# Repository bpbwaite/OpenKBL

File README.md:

# Open Keyboard Lights

OpenKeyBoardLights (okbl) is an embedded project for MIDI piano keyboards. \
The device sits above the keys of an 88-key piano, and illuminates when keys are played. \
To get the cost down, the light strip is mounted across 8 smaller PCBs that are soldered together. It's less expensive than some commercial options, and has more features!

*Technologies:* ESP32-C3, PlatformIO, KiCAD 10 - [Custom PCB](piano-pcb/), and a [3D printable case](models/)

## Usage

Revision 0:
- Turn the encoder to set the brightness.
- Press the encoder to open the settings menu
    - Press a lit key to change and preview its corresponding option.

## Roadmap

| Hardware Feature | Implemented |
|-|-|
| Accurate LED spacing | ✅ |
| Low resistance traces | ✅ |
| Newly improved PCB | 🚧 |
---
| Software Feature | Implemented |
|-|-|
| Various color modes | ✅ more coming soon |
| Demo mode (5 min timer) | ✅ |
| Control over serial | ✅ |
| Control with desktop app | 🚧 |
| Control over WiFi | 🚧 |
| Training mode | 🚧 |
| Hand mode (blue-green) neural model | 🚧 |
---

## Flash Binary

With PlatformIO (recommended):
```
cd keyboard-lights-firmware/
pio run -e release_seeed_xiao_esp32c3 -t upload
```
With esptool v4+, using a prebuilt image:
```
esptool.py --chip esp32c3 --port COMx --baud 460800 write_flash --flash_mode dio --flash_freq 80m --flash_size 4MB 0x0 okbl-firmware-<version>-merged.bin

```

## Building

- Open [keyboard-lights-firmware/](keyboard-lights-firmware/) with PlatformIO
- Set `-DPCB_REVISION` in `platformio.ini` to match your board.
- For testing without a piano, build with `-DKBL_USB_MIDI_DEBUG`. Type `help` to list commands.

## Assembly

- still todo: BOM, gerbers

## Credits

This project is MIT licensed, see [LICENSE](LICENSE). The firmware images include code from these
projects, each under its own license:

- [FastLED](https://github.com/FastLED/FastLED): MIT
- [Arduino MIDI Library](https://github.com/FortySevenEffects/arduino_midi_library): MIT
- [Arduino core for ESP32](https://github.com/espressif/arduino-esp32): LGPL-2.1
- [ESP-IDF](https://github.com/espressif/esp-idf): Apache-2.0

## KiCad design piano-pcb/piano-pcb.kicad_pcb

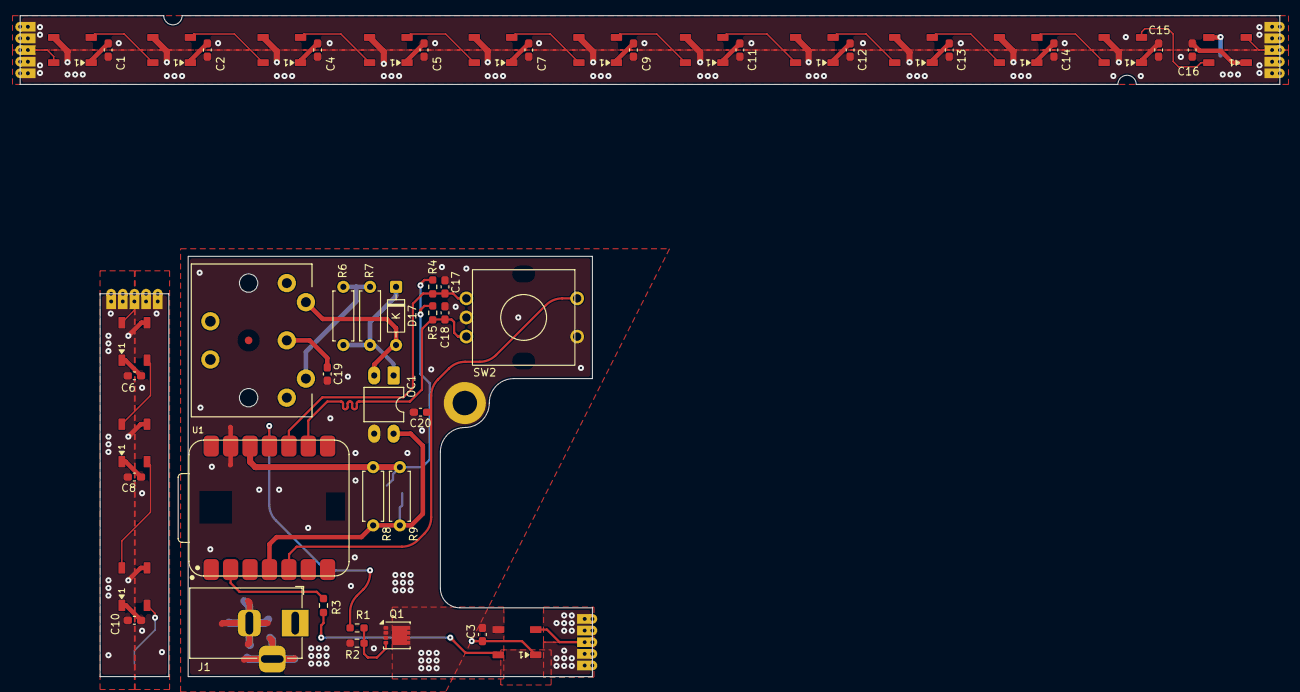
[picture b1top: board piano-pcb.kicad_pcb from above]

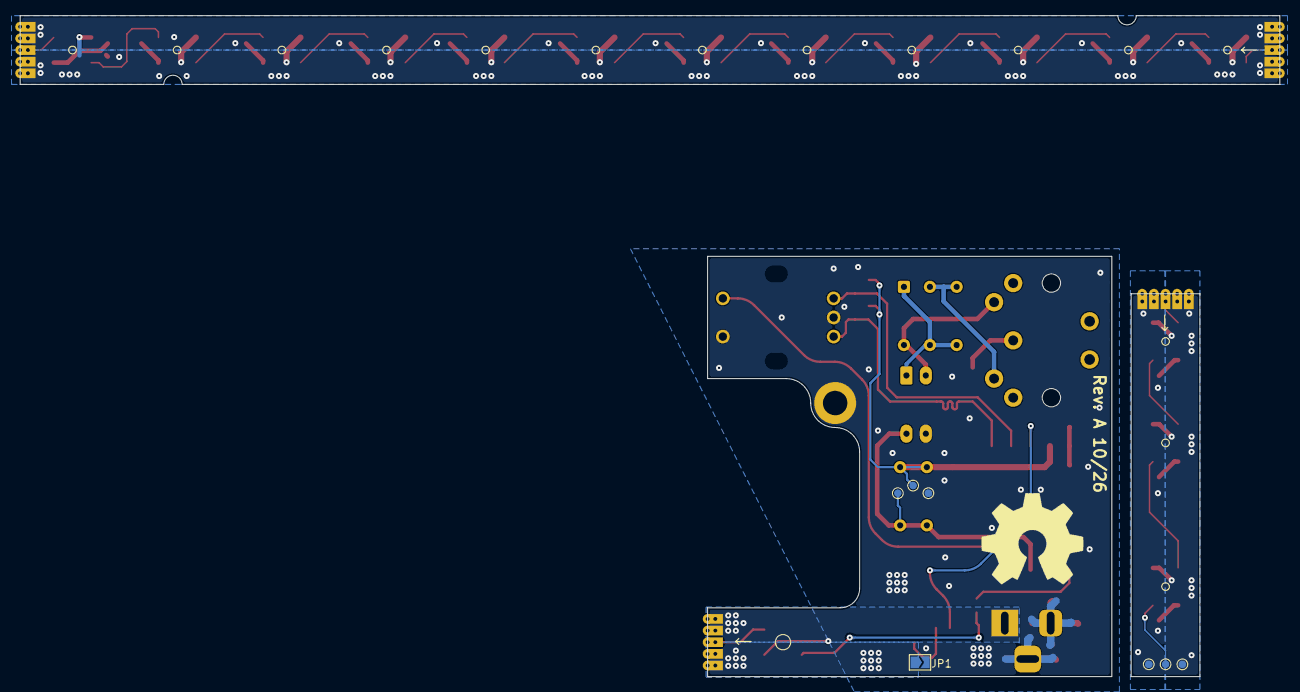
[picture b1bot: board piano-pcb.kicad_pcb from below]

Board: 2 copper layers, 164.9 x 86.5 mm, 66 parts (10 on the bottom side), 35 nets.

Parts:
C1, C2, C3, C4, C5, C6, C7, C8, C9, C10, C11, C12, C13, C14, C15, C16, C19: 100n; C_0603_1608Metric_Pad1.08x0.95mm_HandSolder
C17, C18, C20: 10n; C_0603_1608Metric_Pad1.08x0.95mm_HandSolder
D1, D2, D3, D4, D5, D6, D7, D8, D9, D10, D11, D12, D13, D14, D15, D16: WS2812B; LED_WS2812B_PLCC4_5.0x5.0mm_P3.2mm
D17: 1N914; D_DO-35_SOD27_P7.62mm_Horizontal
FID1: Fiducial; Fiducial_1mm_Mask3mm
H1: MountingHole_Pad; MountingHole_3.2mm_M3_ISO14580_Pad
J1: Barrel_Jack_MountingPin; BarrelJack_Horizontal
J2, J3, J4, J6: Conn_01x05; 1x5_SolderableEdgeConnector
J5: DIN-5_180degree; SameSky_SDS-50J_DIN-5-180_MIDI
JP1: SolderJumper_2_Open; SolderJumper-2_P1.3mm_Open_TrianglePad1.0x1.5mm
OC1: PC817; DIP-4_W7.62mm_LongPads
Q1: CSD17581Q3A; VSON-8_3.3x3.3mm_P0.65mm_NexFET
R1: 330; R_0603_1608Metric_Pad0.98x0.95mm_HandSolder
R2: 100k; R_0603_1608Metric_Pad0.98x0.95mm_HandSolder
R3: TBD; R_0603_1608Metric_Pad0.98x0.95mm_HandSolder
R4, R5: 10k; R_0603_1608Metric_Pad0.98x0.95mm_HandSolder
R6: 1k; R_Axial_DIN0207_L6.3mm_D2.5mm_P7.62mm_Horizontal
R7, R8: TBD; R_Axial_DIN0207_L6.3mm_D2.5mm_P7.62mm_Horizontal
R9: 680; R_Axial_DIN0207_L6.3mm_D2.5mm_P7.62mm_Horizontal
SW2: RotaryEncoder_Switch; Bourns_PEC11R-4x-Sx_RotaryEncoder
Sw1: Mechanical_Shape; OSHW-Symbol_13.4x12mm_SilkScreen
TP1, TP2, TP3, TP4, TP5, TP6: TestPoint; TestPoint_Pad_D1.0mm
U1: XIAO-RP2040-SMD

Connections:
+5V: C1.1, C2.1, C3.1, C4.1, C5.1, C6.1, C7.1, C8.1, C9.1, C10.1, C11.1, C12.1, C13.1, C14.1, C15.1, C16.1, D1.1 (VDD), D2.1 (VDD), D3.1 (VDD), D4.1 (VDD), D5.1 (VDD), D6.1 (VDD), D7.1 (VDD), D8.1 (VDD), D9.1 (VDD), D10.1 (VDD), D11.1 (VDD), D12.1 (VDD), D13.1 (VDD), D14.1 (VDD), D15.1 (VDD), D16.1 (VDD), J1.1, J2.1, J2.2, J3.1, J3.2, J4.1, J4.2, J6.1, J6.2, TP1.1 (1_1)
/MIDI_SHIELD: C19.1, J5.2
/RGB_SIG: R3.1, U1.2 (P27_A1_D1)
GND: C1.2, C2.2, C4.2, C5.2, C6.2, C7.2, C8.2, C9.2, C10.2, C11.2, C12.2, C13.2, C14.2, C15.2, C16.2, D1.3 (VSS), D3.3 (VSS), D4.3 (VSS), D5.3 (VSS), D6.3 (VSS), D7.3 (VSS), D8.3 (VSS), D9.3 (VSS), D10.3 (VSS), D11.3 (VSS), D12.3 (VSS), D13.3 (VSS), D14.3 (VSS), D15.3 (VSS), D16.3 (VSS), J2.4, J2.5, J3.4, J3.5, J6.4, J6.5, TP3.1 (1_1)
GND1: C17.2, C18.2, C19.2, C20.2, H1.1 (1_1), J1.2, J1.MP (MountPin_MP), JP1.2 (B), OC1.3, Q1.1 (S), Q1.2 (S), Q1.3 (S), R2.2, SW2.C, SW2.S2, TP6.1 (1_1), U1.13 (GND)
MIDI_RX: OC1.4, R8.2, R9.2, TP4.1 (1_1), U1.4 (P29_A3_D3)
MIDI_SINK: D17.2 (A), J5.5, OC1.2
MIDI_SOURCE_12V: J5.4, R6.2, R7.2
NEOPIXEL_CONTROLLABLE_GROUND: C3.2, D2.3 (VSS), J4.4, J4.5, JP1.1 (A), Q1.5 (D)
unnamed: D1.4 (DIN), J2.3
unnamed: D1.2 (DOUT), D3.4 (DIN)
unnamed: D3.2 (DOUT), D4.4 (DIN)
unnamed: D4.2 (DOUT), D5.4 (DIN)
unnamed: D5.2 (DOUT), D7.4 (DIN)
unnamed: D6.4 (DIN), J3.3
unnamed: D6.2 (DOUT), D8.4 (DIN)
unnamed: D7.2 (DOUT), D9.4 (DIN)
unnamed: D8.2 (DOUT), D10.4 (DIN)
unnamed: D10.2 (DOUT), TP2.1 (1_1)
unnamed: D9.2 (DOUT), D11.4 (DIN)
unnamed: D11.2 (DOUT), D12.4 (DIN)
unnamed: D12.2 (DOUT), D13.4 (DIN)
unnamed: D13.2 (DOUT), D14.4 (DIN)
unnamed: D14.2 (DOUT), D15.4 (DIN)
unnamed: D15.2 (DOUT), D16.4 (DIN)
unnamed: D16.2 (DOUT), J6.3
unnamed: D17.1 (K), OC1.1, R6.1, R7.1
unnamed: Q1.4 (G), R1.1, R2.1
PSU_ENABLE: R1.2, U1.11 (P3_D10_MOSI)
RGB_DATA: D2.4 (DIN), R3.2
RGB_DATA_OUT: D2.2 (DOUT), J4.3
ROT_A: C17.1, R4.2, SW2.A, U1.10 (P4_D9_MISO)
ROT_B: C18.1, R5.2, SW2.B, U1.9 (P2_D8_SCK)
ROT_SW: C20.1, SW2.S1, U1.5 (P6_SDA_D4)
VDDIO: R4.1, R5.1, R8.1, R9.1, TP5.1 (1_1), U1.12 (3V3)
